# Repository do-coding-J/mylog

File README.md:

# mylog

```
this is study log out of work
```

open remote test

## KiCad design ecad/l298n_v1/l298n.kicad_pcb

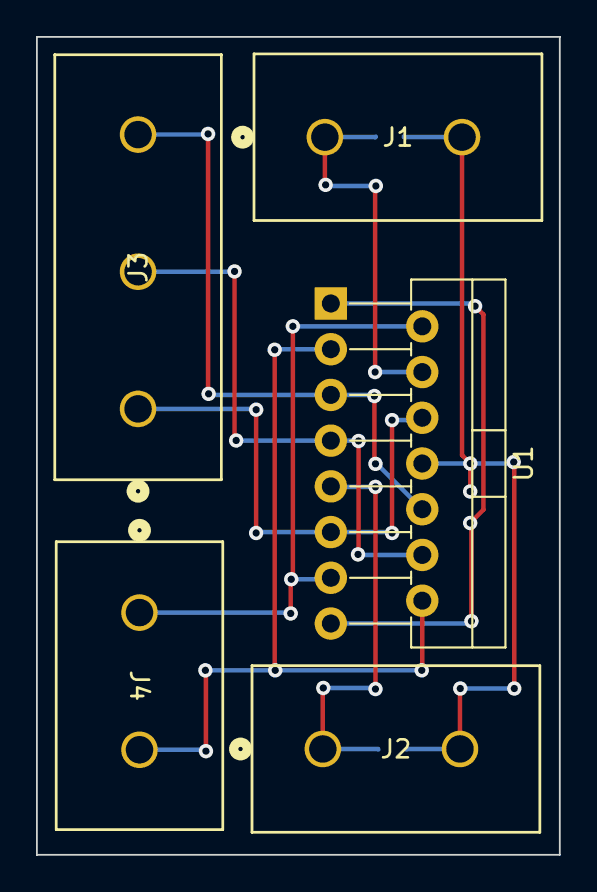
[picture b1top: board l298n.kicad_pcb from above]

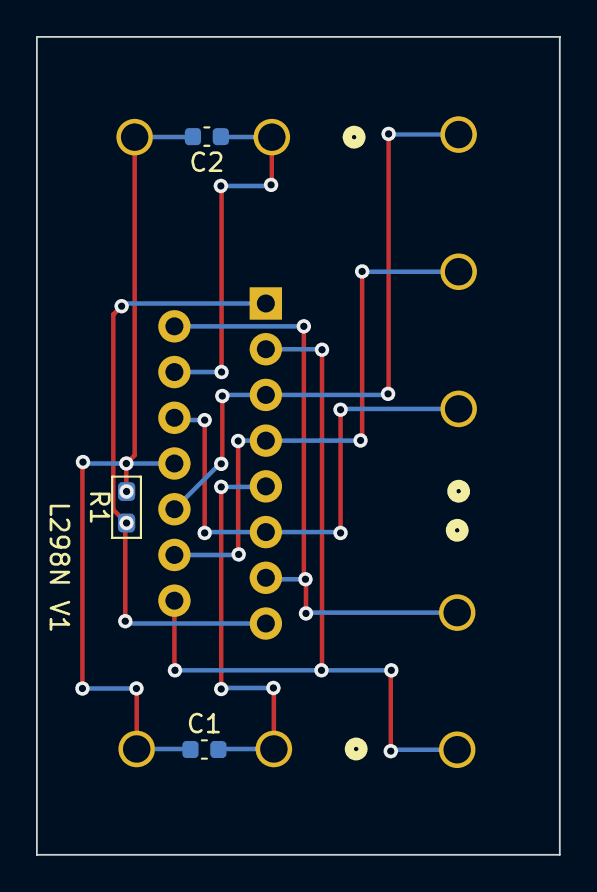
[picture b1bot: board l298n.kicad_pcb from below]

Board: 2 copper layers, 29.0 x 45.4 mm, 8 parts (3 on the bottom side), 9 nets.

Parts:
C1, C2: 100nF; C_0603_1608Metric
J1, J2, J4: 282845-2; CONN2_282845-2_TEC
J3: 282845-3; CONN3_282845-3_TEC
R1: 0.25; R_0603_1608Metric_Pad1.05x0.95mm
U1: L298N; TO-220-15_P2.54x2.54mm_StaggerOdd_Lead4.58mm_Vertical

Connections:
/l298/5V: C1.2, J2.1, U1.9 (Vss)
/l298/12V: C2.1, J1.1, U1.4 (Vs)
/l298/Enable: J3.1, U1.6 (EnA), U1.11 (EnB)
/l298/IN1: J3.3, U1.5 (IN1), U1.10 (IN3)
/l298/IN2: J3.2, U1.7 (IN2), U1.12 (IN4)
/l298/OUT_A: J4.1, U1.2 (OUT1), U1.13 (OUT3)
/l298/OUT_B: J4.2, U1.3 (OUT2), U1.14 (OUT4)
/l298/SENSE: R1.1, U1.1 (SENSE_A), U1.15 (SENSE_B)
GND: C1.1, C2.2, J1.2, J2.2, R1.2, U1.8 (GND)

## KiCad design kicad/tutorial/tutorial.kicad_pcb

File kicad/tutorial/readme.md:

# 회로 공부를 시작해보자

## 무엇을 만들기 고민해보자

### 시건 장치
- 번호 입력 또는 통신을 통해 잠금/해제하는 장치

#### 플로우

```mermaid
flowchart TD
A[번호키 입력]
B[블루투스 통신 입력]
D[잠금 해제]
G[잠금]
H[문 닫음]
C{서버 인증}
E{센서 인식}
F{2초 타이머}

H-->E
A-->C
B--열림-->D
B--잠김--> E
C--yes-->D
D-->E
E--yes--> F
E--no--> D
F --> G
```

#### 필요한 구성요소
1. MCU
- uart 지원 (bluetooth, wifi)
- pwm 지원 (servo motor)
2. bluetooth module
3. wifi module
4. servo motor x2
5. IR sensor(ant detecting sensor possible) x2
6. key pad module

#### 회로도
대충 그림

#### Foot Print
표시만 함 (에러)

#### pcb
(에러)

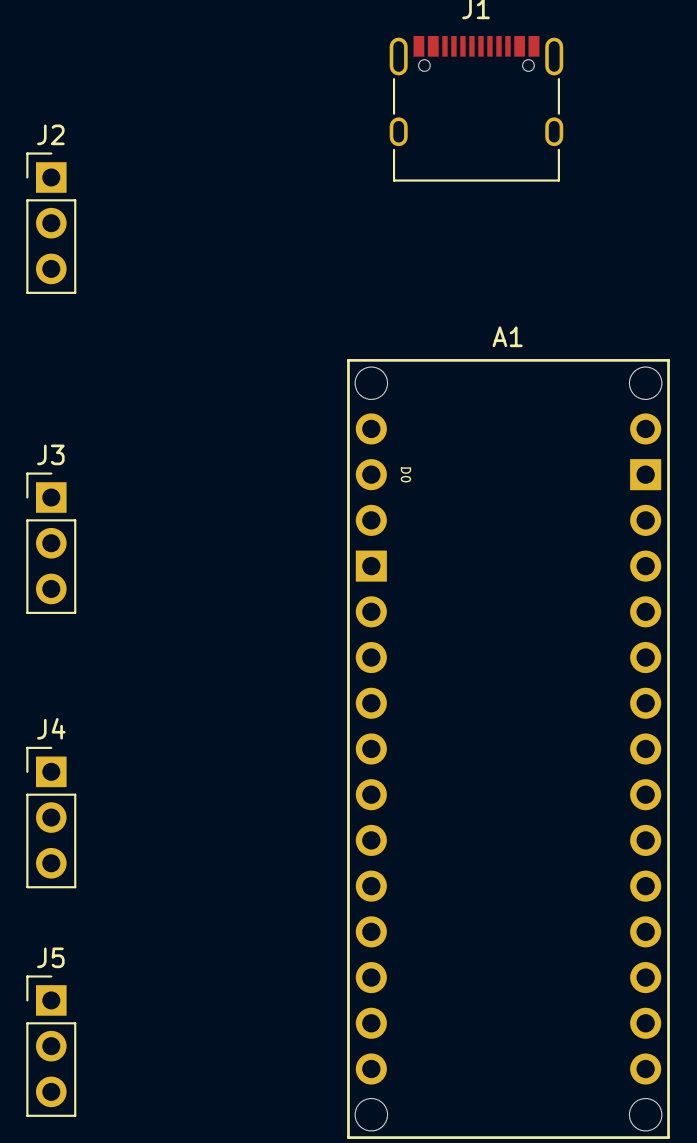
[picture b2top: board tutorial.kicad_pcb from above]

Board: 2 copper layers, 7 parts (0 on the bottom side), 6 nets, no tracks yet.

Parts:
A1: Arduino_Nano_Socket
A2: Bluetooth_Serial
J1: USB_C_Receptacle_PowerOnly_6P; USB_C_Receptacle_XKB_U262-16XN-4BVC11
J2, J3, J4, J5: Conn_01x03; PinHeader_1x03_P2.54mm_Vertical

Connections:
GND: A1.GND1 (GND), A1.GND2 (GND), J1.A5 (CC1), J1.A12 (GND), J1.B5 (CC2), J1.B12 (GND), J1.S1 (SHIELD), J2.3, J3.3, J4.3, J5.3
IR1: A1.D5, J4.1
IR2: A1.D7, J5.1
POWER: A1.VIN, J1.A9 (VBUS), J1.B9 (VBUS), J2.2, J3.2, J4.2, J5.2
SERVO1: A1.D6, J2.1
SERVO2: A1.D8, J3.1

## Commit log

2023-05-02 sock ch2
2023-05-08 blah
2023-05-08 ch6 done
2023-05-11 empty
2023-05-14 combine
2023-05-15 install.md
2023-05-17 rebase
2023-05-19 install update
2023-05-27 ch 10 continue
2023-06-11 push
2023-06-11 multi echo server
2023-06-22 pipe
2023-06-23 test
2023-06-28 re added
2023-08-17 sh file added
2023-08-18 icarus
2023-09-20 project planning
2023-09-20 schemetic start
2023-09-20 foot print error
2023-09-22 spice
2023-09-24 verilog pdf studying
2023-11-12 new proj
2023-11-12 new readme
2023-11-12 why not
2023-11-12 component added
2023-11-13 folowup :
2023-12-22 copy study
2024-01-01 html start
2024-01-01 backup
2024-01-28 stm32f401rb
2024-03-16 automation start
2024-03-16 key added
2024-03-16 homework
2024-03-16 sub indicators
2024-03-17 need strategy
2024-03-21 bolinger done
2024-03-23 algorithm fix
2024-03-27 logicing
2024-03-30 no buying algorithm
2024-04-01 check log
2024-04-30 l298 v1 added
2024-04-30 wifi direct
2024-05-02 env error
2024-05-02 add proj
2024-05-02 여기까지
2024-05-12 ap and sta
2024-05-18 linux add
2024-06-24 makefile tutorial added
